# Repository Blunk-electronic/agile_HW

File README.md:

# Demo Project to demonstrate Agile Hardware Development

## Installation
After cloning the repository you have the demo design ready for use.
So far no installation is required.
If you need the module instantiation tool run in the base directory

```
sh install.sh
```

This installs the script [instantiate](instantiate) in your $HOME/bin.

## Module Instantiation

The script script [instantiate](instantiate) renames nets of a module so that
the user is not required to edit them manually via the grapical user interface.
It creates a new schematic and board file with a desired index. 
It requires arguemts in a fixed order. The explanation comes via an example:
```
instantiate led_driver_1.sch LED_DRV 1 3
```
The first argument is the name of the schematic file name. In our case it is led_driver_1.sch.
This file and the associated board file led_driver_1.brd must exist already. It can be regarded
as the generic module.
The second argument LED_DRV is a general prefix that have some net names inside the module.
There is for example a net LED_DRV_1_IN. 
3rd argument is the input index. Prefix and input index compose a string like LED_DRV_1.
The script searches nets that start with the prefix LED_DRV_1 and renames them using
the output index, given by the 4th argument, to LED_DRV_3. Other net names like GND or P3V3
are left as they are.
So the net LED_DRV_1_IN will be renamed to LED_DRV_3_IN.
The script does NOT modify the generic module. It creates a new schematic
and a new board file named led_driver_3.sch and led_driver_3.brd.

The console output is show below:

```
$ instantiate led_driver_1.sch LED_DRV 1 3
input module   : led_driver_1.sch
net prefix     : LED_DRV
index in       : 1
index out      : 3
prefix in full : LED_DRV_1
prefix out full: LED_DRV_3
processing schematic ...
- renaming net LED_DRV_1_IN to LED_DRV_3_IN
- renaming net LED_DRV_1_B to LED_DRV_3_B
- renaming net LED_DRV_1_C to LED_DRV_3_C
- renaming net LED_DRV_1_OUT to LED_DRV_3_OUT
- renaming net LED_DRV_1_IN to LED_DRV_3_IN
processing board ...
- renaming net LED_DRV_1_IN to LED_DRV_3_IN
- renaming net LED_DRV_1_B to LED_DRV_3_B
- renaming net LED_DRV_1_C to LED_DRV_3_C
- renaming net LED_DRV_1_OUT to LED_DRV_3_OUT
generated files:
schematic: led_driver_3.sch
board    : led_driver_3.brd
```

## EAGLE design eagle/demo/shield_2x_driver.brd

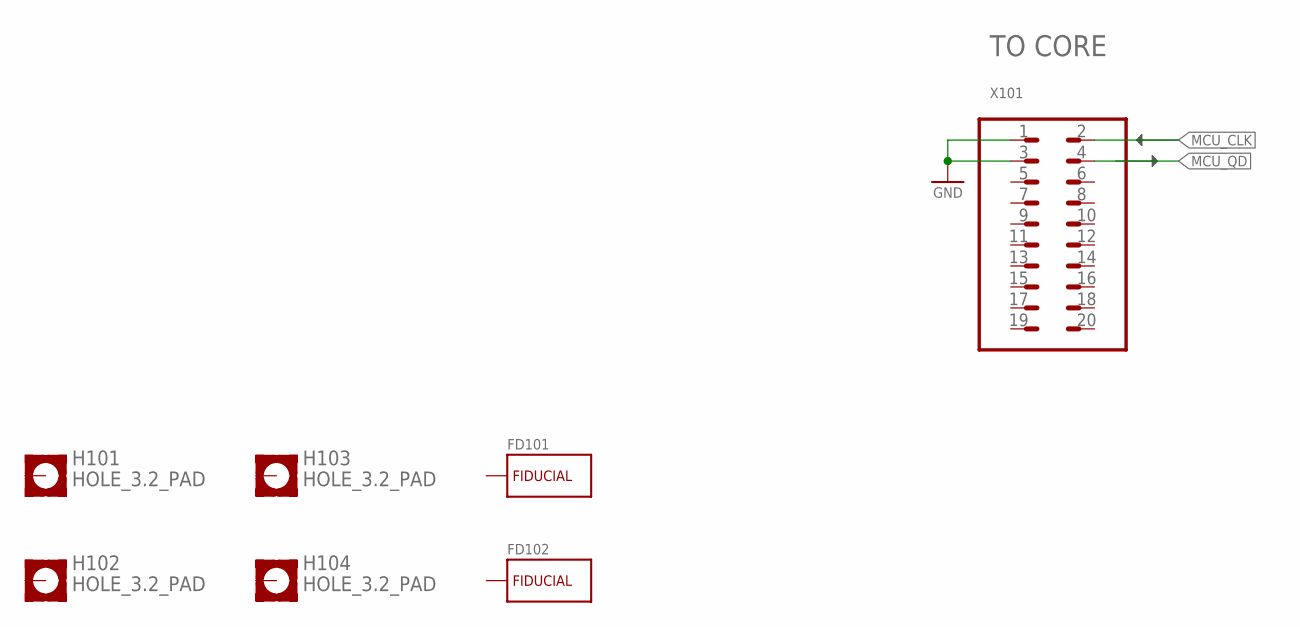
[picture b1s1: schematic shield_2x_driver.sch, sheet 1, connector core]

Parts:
FD101, FD102: FIDUCIAL_CROSSHAIR; CROSSHAIR
H101, H102, H103, H104: HOLE_3.2_PAD; 3.2_PAD
X101: MALE_2X10-T-VERTICAL_2.54MM; T_MALE_2X10_VERTICAL_GRID_2.54MM; PART_CODE_BEL X_PAC_T_MALE_2X10_VERTICAL_PITCH_2mm54

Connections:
GND: X101.1, X101.3; also elsewhere on the board
MCU_CLK: X101.2; also elsewhere on the board
MCU_QD: X101.4; also elsewhere on the board

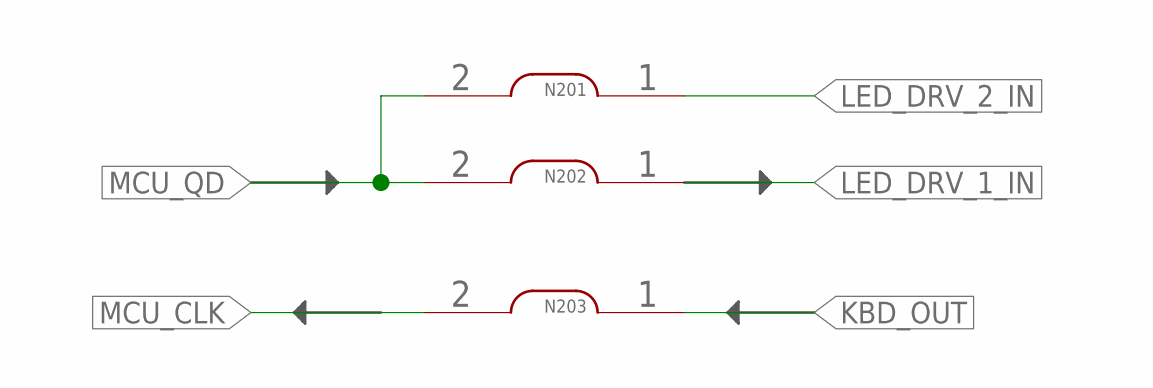
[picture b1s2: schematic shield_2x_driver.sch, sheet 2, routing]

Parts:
N201, N202: NET_CHANGER-S-0.3MM; S_NET_CHANGER_0.3MM
N203: NET_CHANGER-S-0.15MM; S_NET_CHANGER_0.15MM

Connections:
KBD_OUT: N203.1; also elsewhere on the board
LED_DRV_1_IN: N202.1; also elsewhere on the board
LED_DRV_2_IN: N201.1; also elsewhere on the board
MCU_CLK: N203.2; also elsewhere on the board
MCU_QD: N201.2, N202.2; also elsewhere on the board

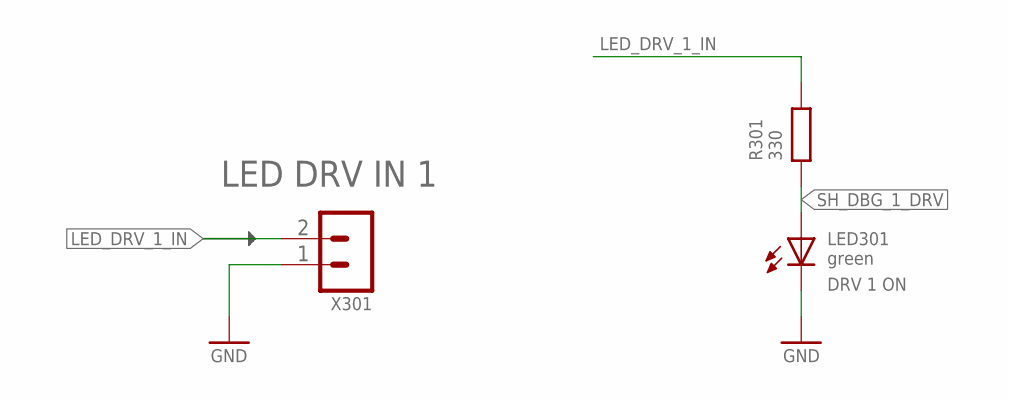
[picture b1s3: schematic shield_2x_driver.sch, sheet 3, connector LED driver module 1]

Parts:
LED301: green; S_0805; PART_CODE_BEL LED_PAC_S_0805_VAL_green
R301: 330; S_0805; PART_CODE_BEL R_PAC_S_0805_VAL_330
X301: MALE_2X1-T-VERTICAL; T_MALE_2X1_VERTICAL_PITCH_2MM54

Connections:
GND: LED301.C, X301.1; also elsewhere on the board
LED_DRV_1_IN: R301.2, X301.2; also elsewhere on the board
SH_DBG_1_DRV: LED301.A, R301.1

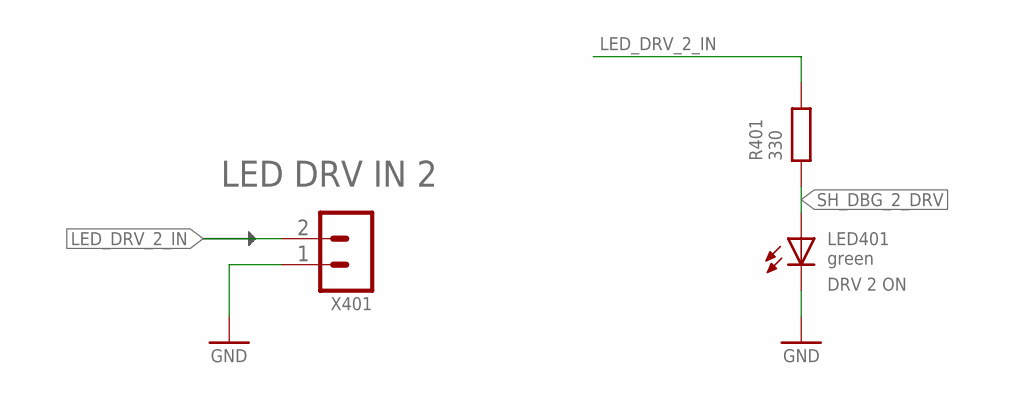
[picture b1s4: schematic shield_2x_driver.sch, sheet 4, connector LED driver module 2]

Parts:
LED401: green; S_0805; PART_CODE_BEL LED_PAC_S_0805_VAL_green
R401: 330; S_0805; PART_CODE_BEL R_PAC_S_0805_VAL_330
X401: MALE_2X1-T-VERTICAL; T_MALE_2X1_VERTICAL_PITCH_2MM54

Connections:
GND: LED401.C, X401.1; also elsewhere on the board
LED_DRV_2_IN: R401.2, X401.2; also elsewhere on the board
SH_DBG_2_DRV: LED401.A, R401.1

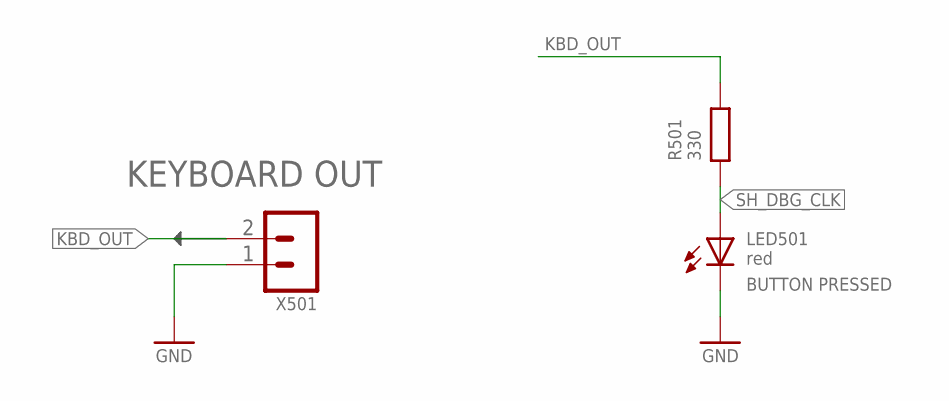
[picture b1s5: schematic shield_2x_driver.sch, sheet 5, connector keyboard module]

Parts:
LED501: red; S_0805; PART_CODE_BEL LED_PAC_S_0805_VAL_red
R501: 330; S_0805; PART_CODE_BEL R_PAC_S_0805_VAL_330
X501: MALE_2X1-T-VERTICAL; T_MALE_2X1_VERTICAL_PITCH_2MM54

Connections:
GND: LED501.C, X501.1; also elsewhere on the board
KBD_OUT: R501.2, X501.2; also elsewhere on the board
SH_DBG_CLK: LED501.A, R501.1

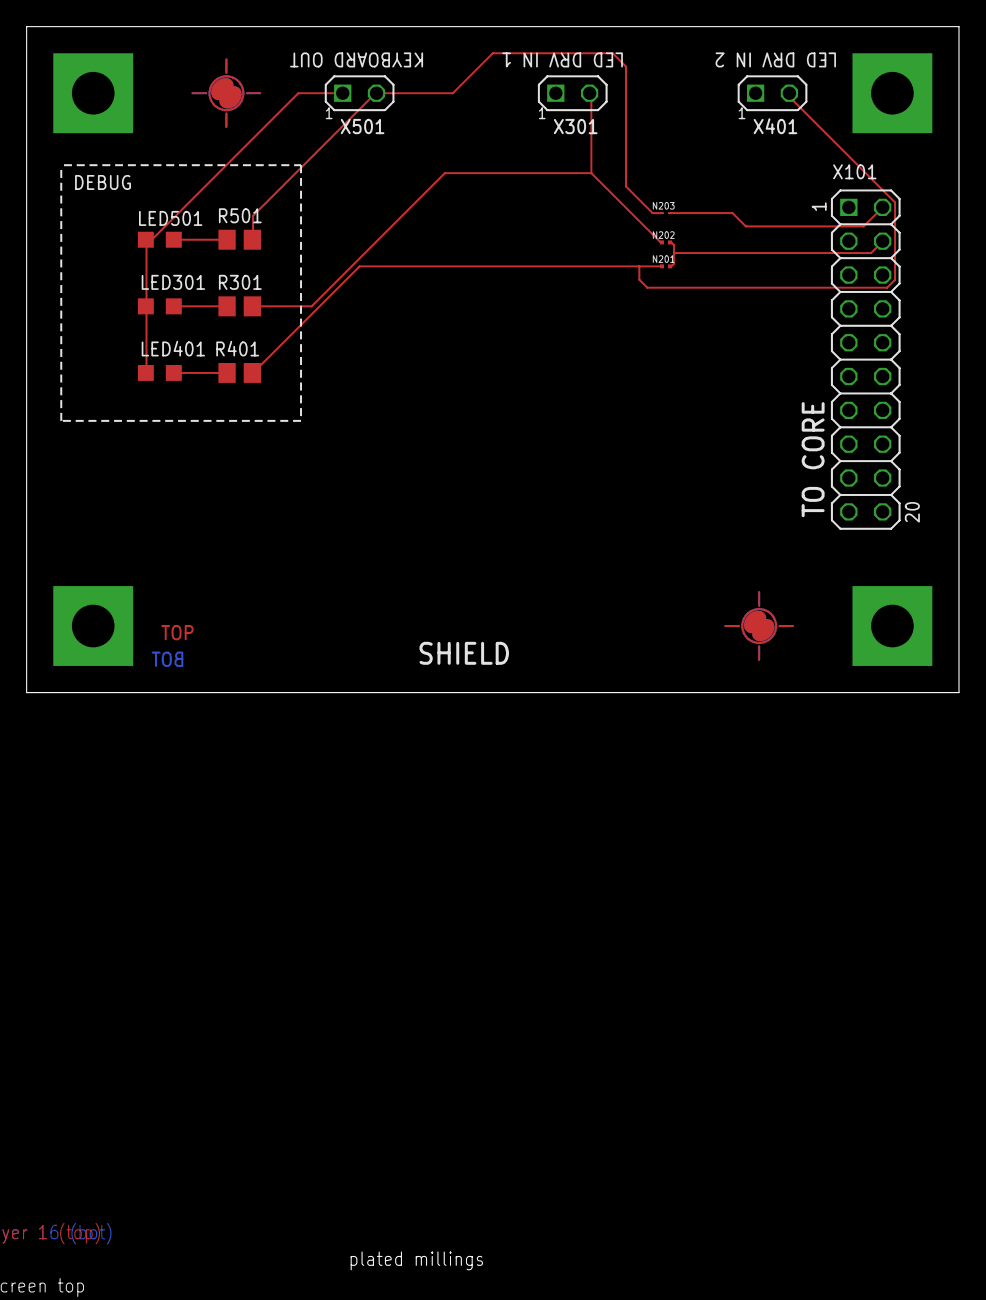
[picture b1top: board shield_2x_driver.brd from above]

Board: 4 copper layers, 70.0 x 93.6 mm, 20 parts (0 on the bottom side), 9 nets.

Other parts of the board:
U$9: A4_LANDSCAPE

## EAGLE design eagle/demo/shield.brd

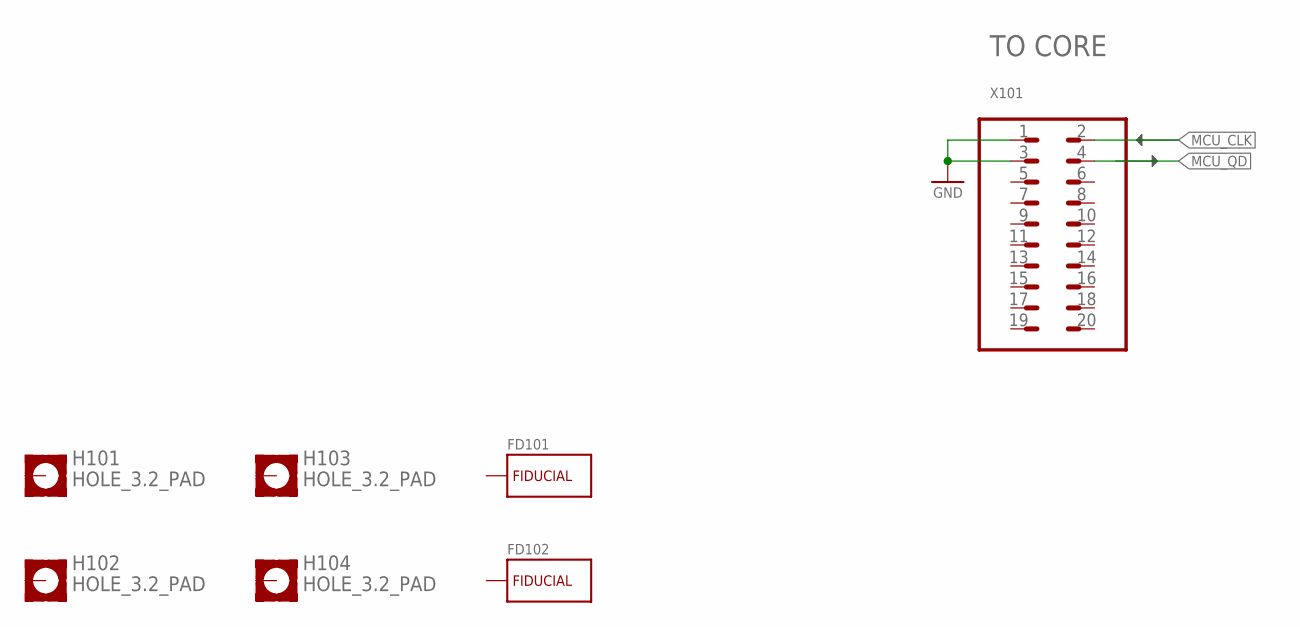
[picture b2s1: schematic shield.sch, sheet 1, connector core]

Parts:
FD101, FD102: FIDUCIAL_CROSSHAIR; CROSSHAIR
H101, H102, H103, H104: HOLE_3.2_PAD; 3.2_PAD
X101: MALE_2X10-T-VERTICAL_2.54MM; T_MALE_2X10_VERTICAL_GRID_2.54MM; PART_CODE_BEL X_PAC_T_MALE_2X10_VERTICAL_PITCH_2mm54

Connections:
GND: X101.1, X101.3; also elsewhere on the board
MCU_CLK: X101.2; also elsewhere on the board
MCU_QD: X101.4; also elsewhere on the board

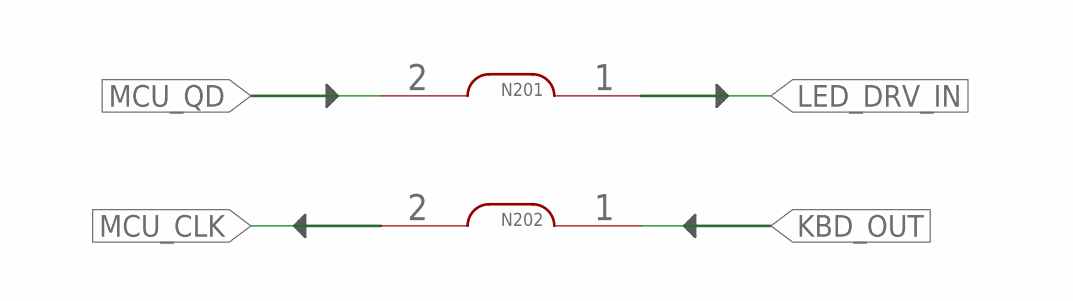
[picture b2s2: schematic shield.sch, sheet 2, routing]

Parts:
N201: NET_CHANGER-S-0.3MM; S_NET_CHANGER_0.3MM
N202: NET_CHANGER-S-0.15MM; S_NET_CHANGER_0.15MM

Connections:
KBD_OUT: N202.1; also elsewhere on the board
LED_DRV_IN: N201.1; also elsewhere on the board
MCU_CLK: N202.2; also elsewhere on the board
MCU_QD: N201.2; also elsewhere on the board

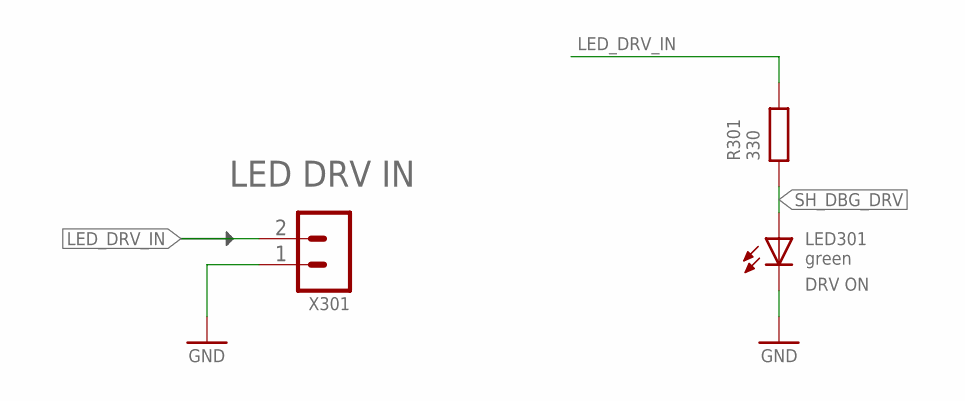
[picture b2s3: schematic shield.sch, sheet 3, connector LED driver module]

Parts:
LED301: green; S_0805; PART_CODE_BEL LED_PAC_S_0805_VAL_green
R301: 330; S_0805; PART_CODE_BEL R_PAC_S_0805_VAL_330
X301: MALE_2X1-T-VERTICAL; T_MALE_2X1_VERTICAL_PITCH_2MM54

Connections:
GND: LED301.C, X301.1; also elsewhere on the board
LED_DRV_IN: R301.2, X301.2; also elsewhere on the board
SH_DBG_DRV: LED301.A, R301.1

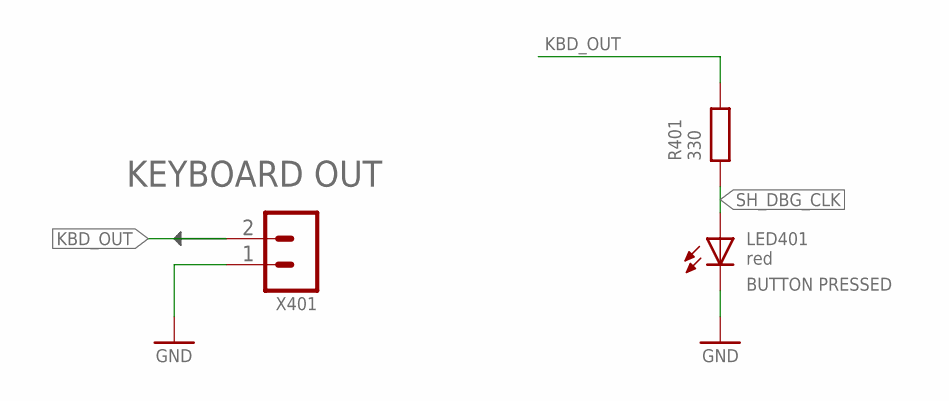
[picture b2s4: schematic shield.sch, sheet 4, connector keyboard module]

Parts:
LED401: red; S_0805; PART_CODE_BEL LED_PAC_S_0805_VAL_red
R401: 330; S_0805; PART_CODE_BEL R_PAC_S_0805_VAL_330
X401: MALE_2X1-T-VERTICAL; T_MALE_2X1_VERTICAL_PITCH_2MM54

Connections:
GND: LED401.C, X401.1; also elsewhere on the board
KBD_OUT: R401.2, X401.2; also elsewhere on the board
SH_DBG_CLK: LED401.A, R401.1

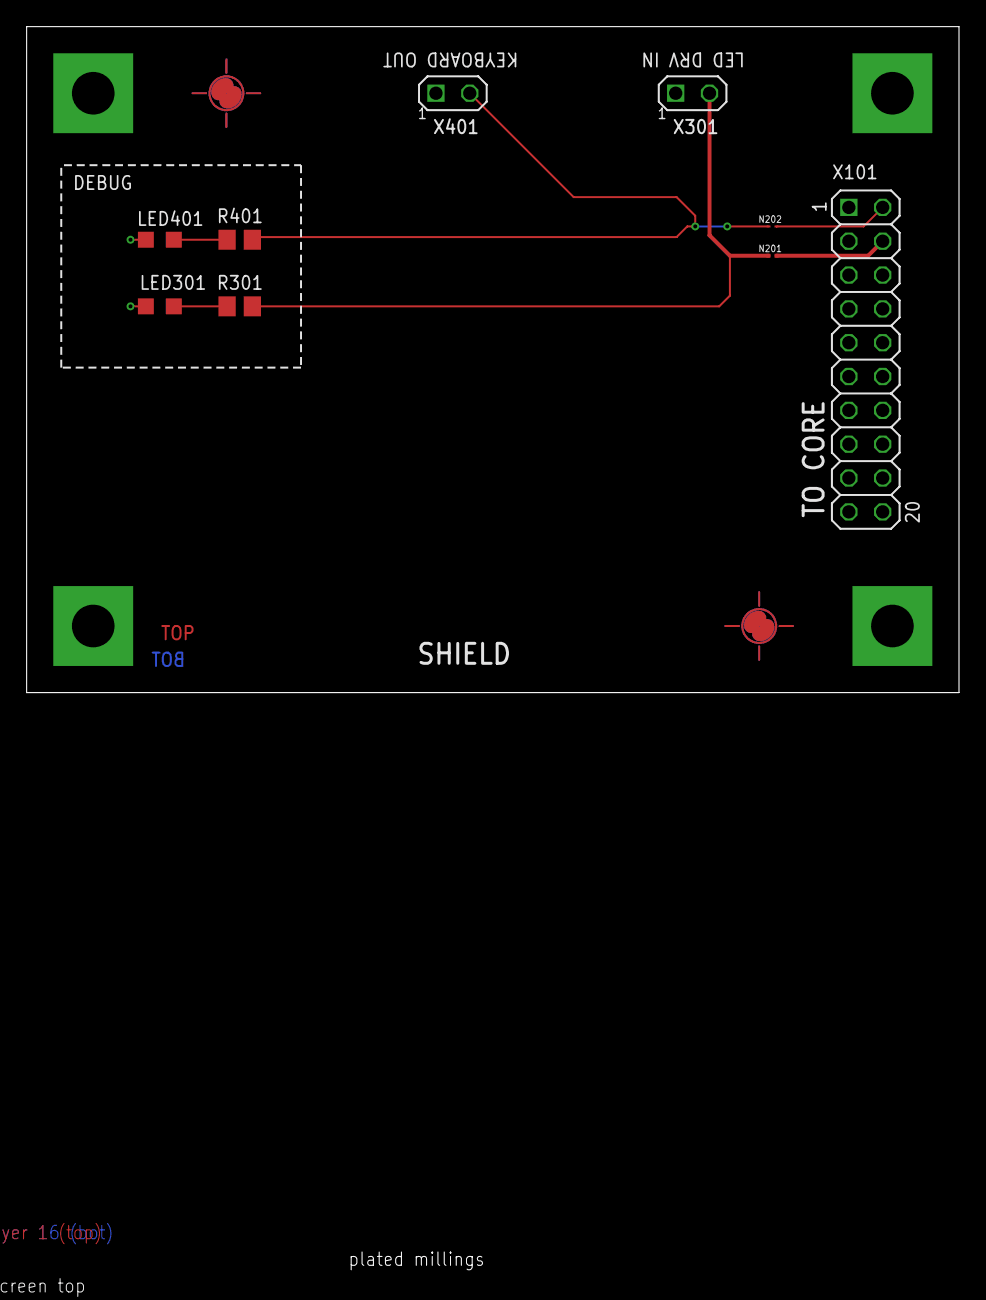
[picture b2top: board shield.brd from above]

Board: 4 copper layers, 70.0 x 93.6 mm, 16 parts (0 on the bottom side), 7 nets.

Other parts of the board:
U$9: A4_LANDSCAPE

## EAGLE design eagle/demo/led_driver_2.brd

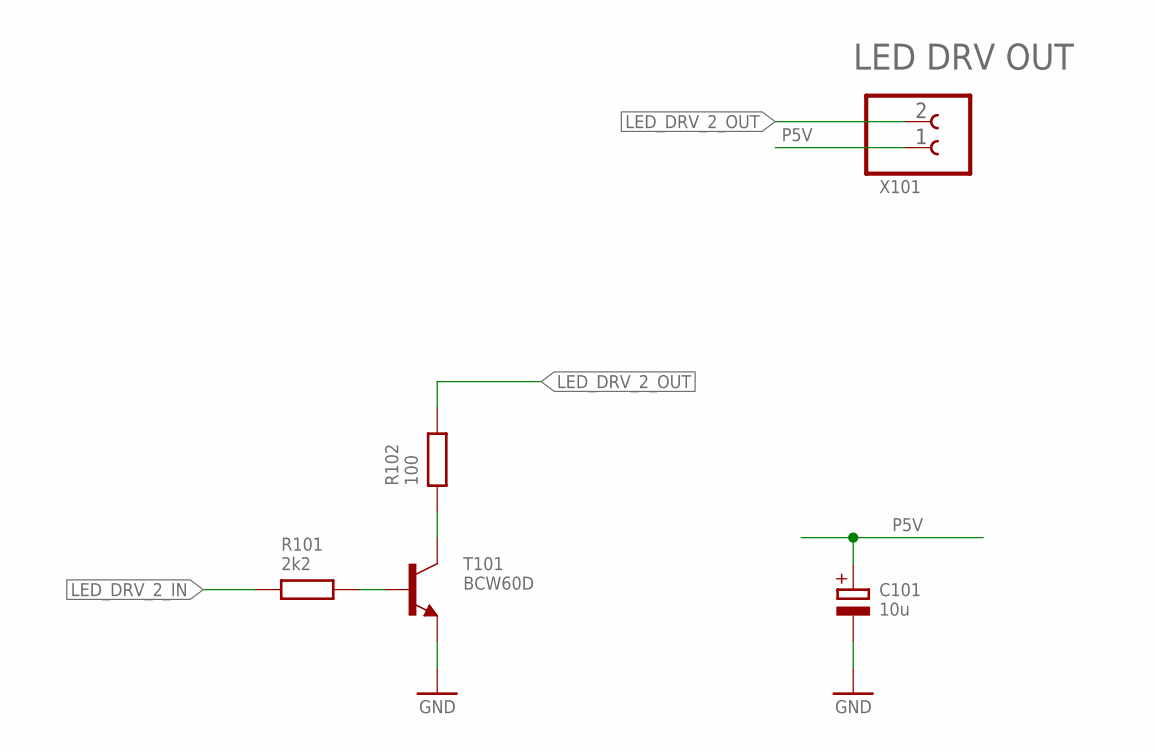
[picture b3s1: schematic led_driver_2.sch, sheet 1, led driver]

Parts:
C101: 10u; S_6032; PART_CODE_BEL C_PAC_S_6032_VAL_10u_Vmax_35V
R101: 2k2; S_0805; PART_CODE_BEL R_PAC_S_0805_VAL_2k2
R102: 100; S_0805; PART_CODE_BEL R_PAC_S_0805_VAL_100
T101: BCW60D; S_SOT23; PART_CODE_BEL T_PAC_S_SOT23_VAL_BCW60D
X101: CLAMP_1X2-T-2.5MM; T_WIRE_CLAMP_1X2_PITCH_2MM5

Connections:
GND: C101.-, T101.2 (E); also elsewhere on the board
LED_DRV_2_B: R101.2, T101.1 (B)
LED_DRV_2_C: R102.1, T101.3 (C)
LED_DRV_2_IN: R101.1; also elsewhere on the board
LED_DRV_2_OUT: R102.2, X101.2
P5V: C101.+, X101.1; also elsewhere on the board

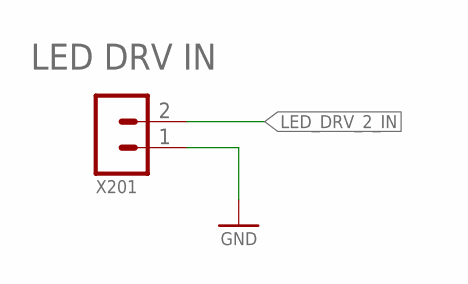
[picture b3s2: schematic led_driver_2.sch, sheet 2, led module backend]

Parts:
X201: MALE_2X1-T-VERTICAL; T_MALE_2X1_VERTICAL_PITCH_2MM54

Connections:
GND: X201.1; also elsewhere on the board
LED_DRV_2_IN: X201.2; also elsewhere on the board

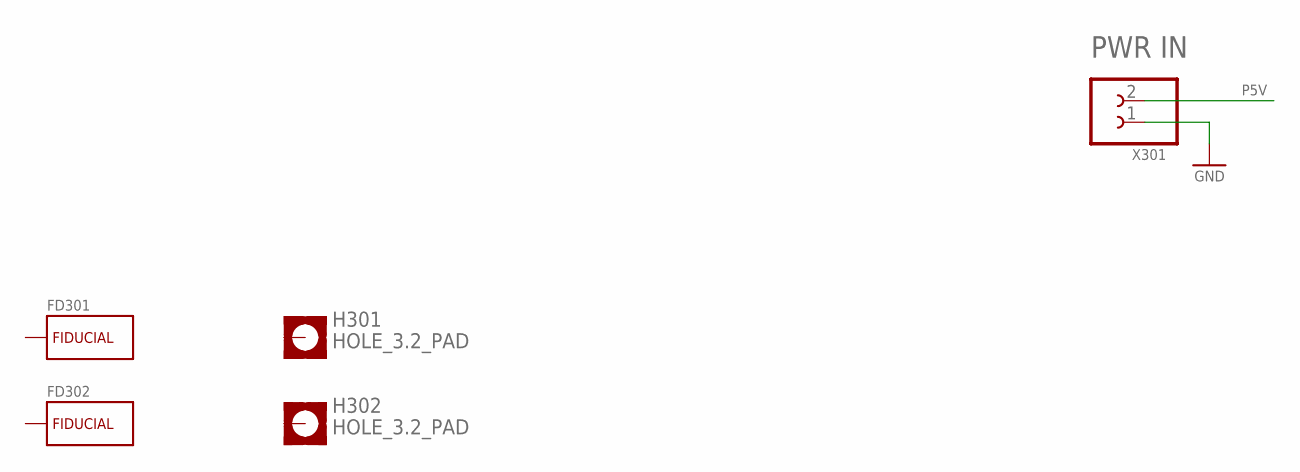
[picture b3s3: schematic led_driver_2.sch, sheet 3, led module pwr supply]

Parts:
FD301, FD302: FIDUCIAL_CROSSHAIR; CROSSHAIR
H301, H302: HOLE_3.2_PAD; 3.2_PAD
X301: CLAMP_1X2-T-2.5MM; T_WIRE_CLAMP_1X2_PITCH_2MM5

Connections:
GND: X301.1; also elsewhere on the board
P5V: X301.2; also elsewhere on the board

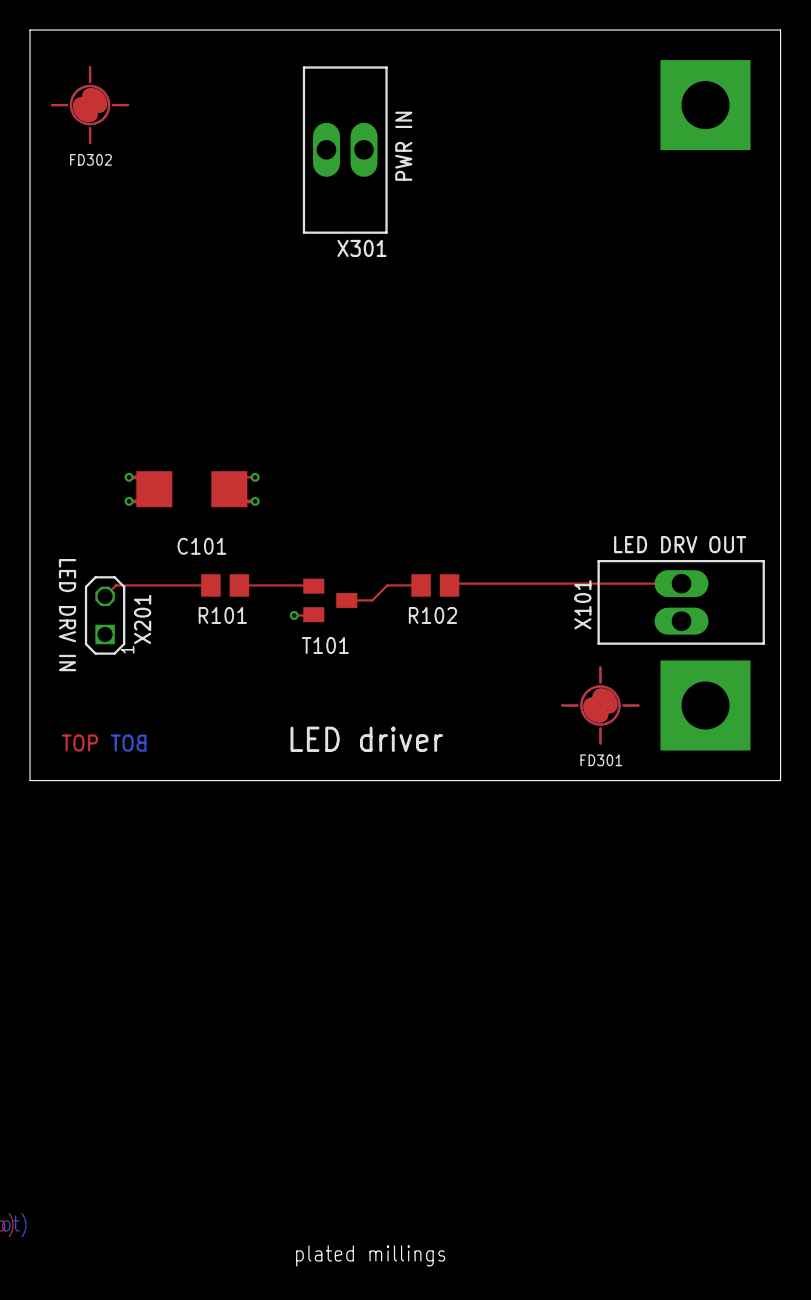
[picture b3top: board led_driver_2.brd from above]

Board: 4 copper layers, 50.0 x 82.6 mm, 12 parts (0 on the bottom side), 6 nets.

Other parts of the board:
U$5: A4_LANDSCAPE

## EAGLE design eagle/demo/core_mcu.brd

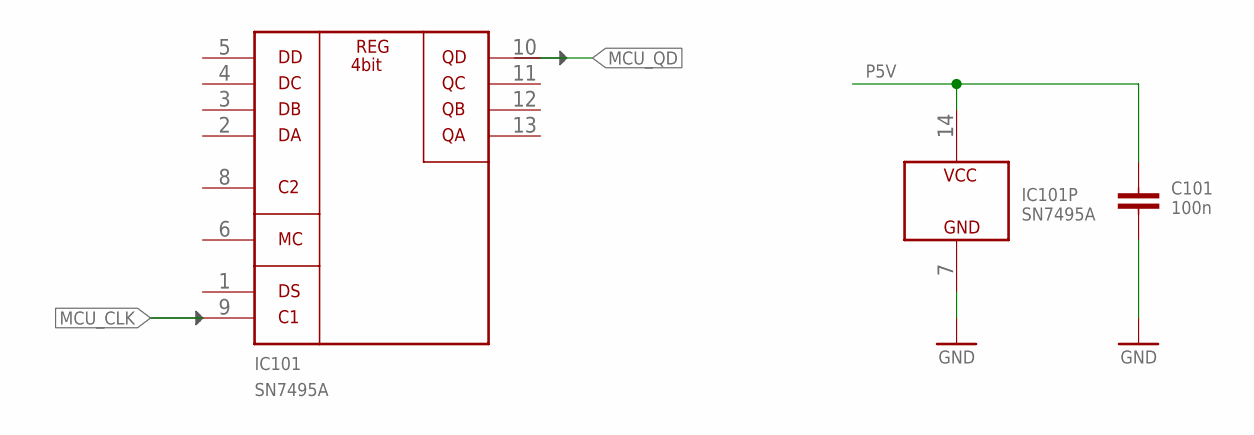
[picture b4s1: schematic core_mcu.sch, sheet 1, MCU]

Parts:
C101: 100n; S_0805; PART_CODE_BEL C_PAC_S_0805_VAL_100n
IC101: SN7495A; T_NDIP14

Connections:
GND: C101.2, IC101.7 (GND); also elsewhere on the board
MCU_CLK: IC101.9 (C1); also elsewhere on the board
MCU_QD: IC101.10 (QD); also elsewhere on the board
P5V: C101.1, IC101.14 (VCC); also elsewhere on the board

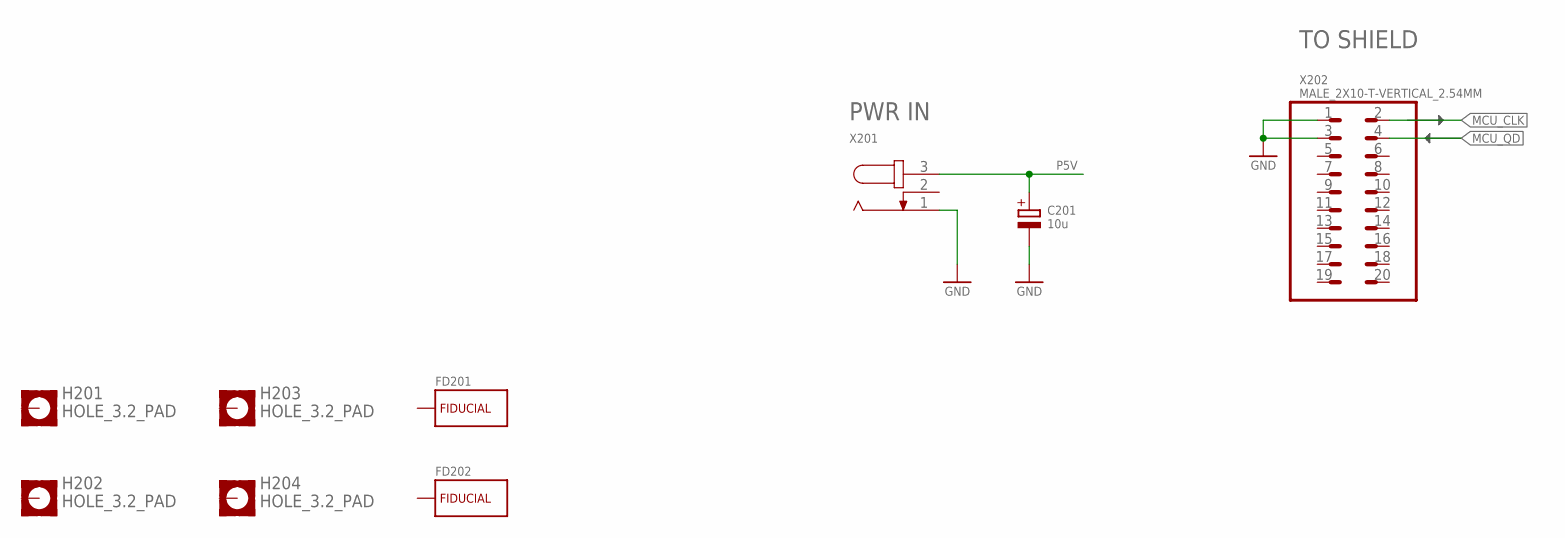
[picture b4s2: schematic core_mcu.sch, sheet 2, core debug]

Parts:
C201: 10u; S_6032; PART_CODE_BEL C_PAC_S_6032_VAL_10u_Vmax_35V
FD201, FD202: FIDUCIAL_CROSSHAIR; CROSSHAIR
H201, H202, H203, H204: HOLE_3.2_PAD; 3.2_PAD
X201: POWER_JACK-T-0; T_POWER_JACK_SPC4077
X202: MALE_2X10-T-VERTICAL_2.54MM; T_MALE_2X10_VERTICAL_GRID_2.54MM; PART_CODE_BEL X_PAC_T_MALE_2X10_VERTICAL_PITCH_2mm54

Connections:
GND: C201.-, X201.1, X202.1, X202.3; also elsewhere on the board
MCU_CLK: X202.2; also elsewhere on the board
MCU_QD: X202.4; also elsewhere on the board
P5V: C201.+, X201.3; also elsewhere on the board

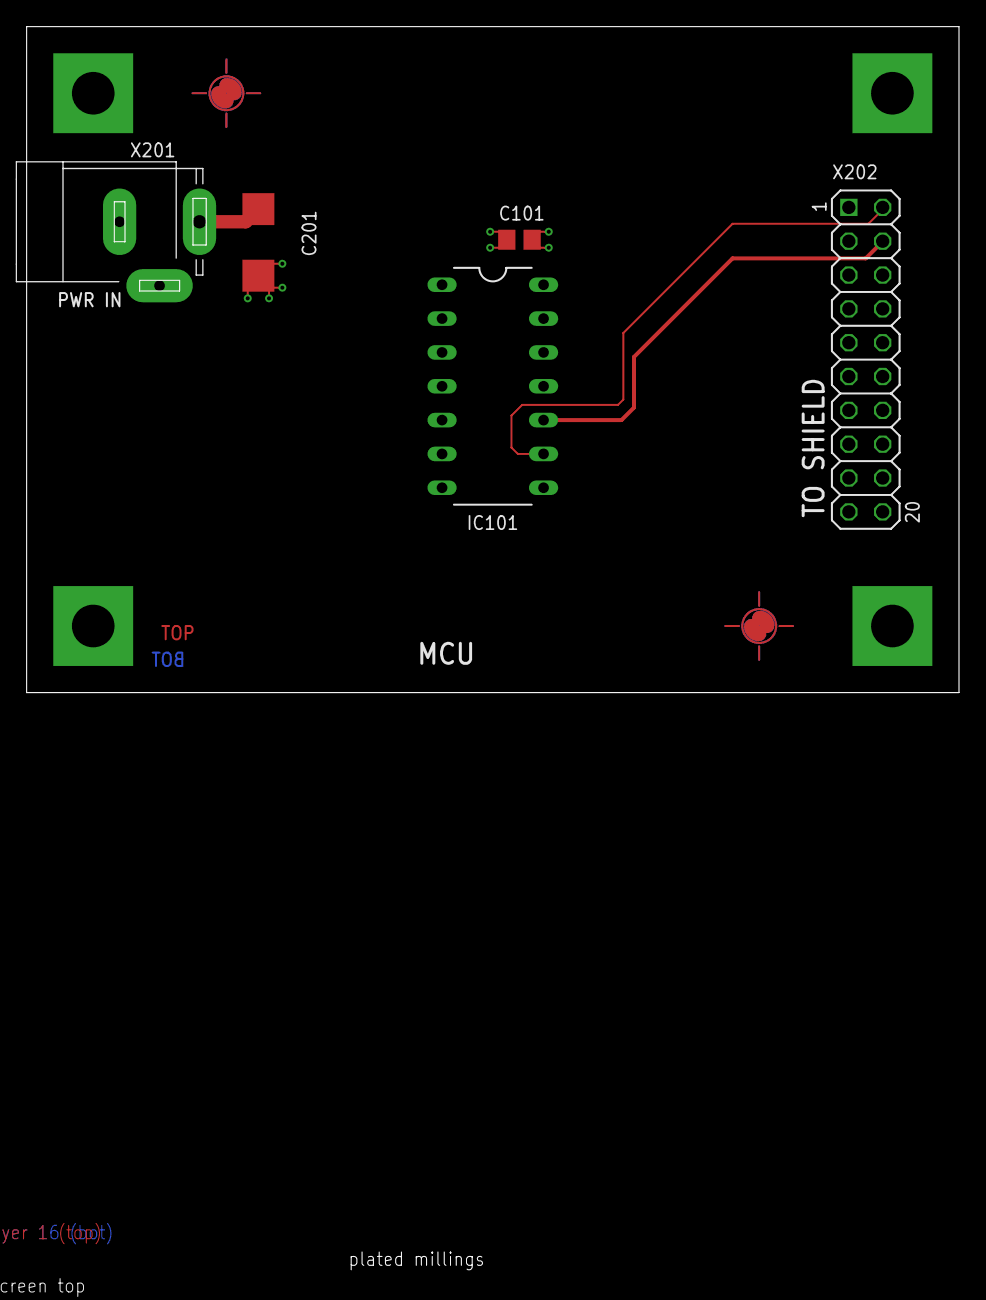
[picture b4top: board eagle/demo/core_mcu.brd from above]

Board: 4 copper layers, 70.0 x 93.6 mm, 12 parts (0 on the bottom side), 4 nets.

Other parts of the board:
U$9: A4_LANDSCAPE

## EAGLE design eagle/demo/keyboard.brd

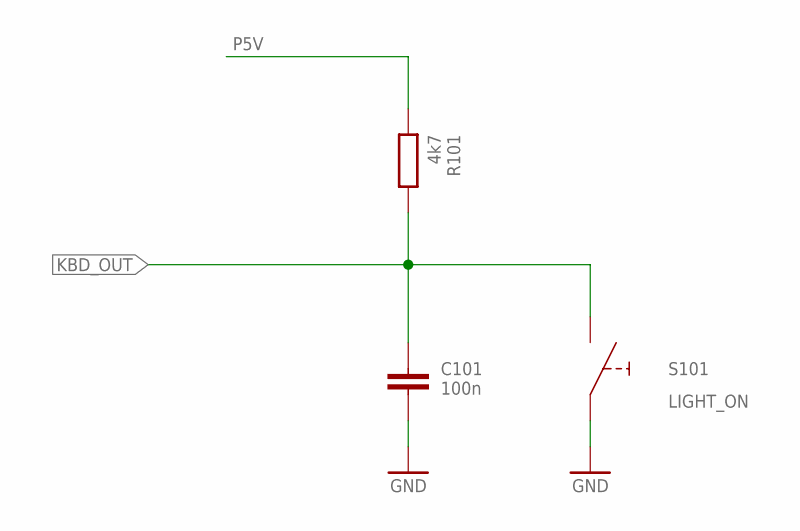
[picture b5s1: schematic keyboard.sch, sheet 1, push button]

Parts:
C101: 100n; S_0805; PART_CODE_BEL C_PAC_S_0805_VAL_100n
R101: 4k7; S_0805; PART_CODE_BEL R_PAC_S_0805_VAL_4k7
S101: PUSH_BUTTON_S_6X6MM; S_PUSH_BUTTON_6X6; PART_CODE_BEL S_PAC_S_PUSH_BUTTON_6X6

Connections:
GND: C101.2, S101.A (A1), S101.A1; also elsewhere on the board
KBD_OUT: C101.1, R101.2, S101.B (B1), S101.B1; also elsewhere on the board
P5V: R101.1; also elsewhere on the board

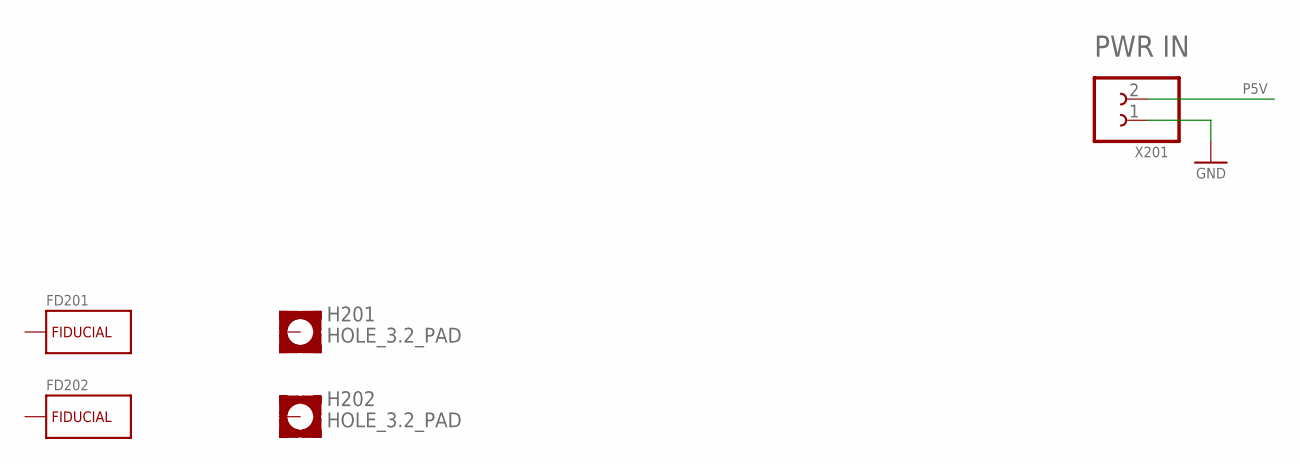
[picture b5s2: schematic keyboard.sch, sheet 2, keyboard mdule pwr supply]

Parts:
FD201, FD202: FIDUCIAL_CROSSHAIR; CROSSHAIR
H201, H202: HOLE_3.2_PAD; 3.2_PAD
X201: CLAMP_1X2-T-2.5MM; T_WIRE_CLAMP_1X2_PITCH_2MM5

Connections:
GND: X201.1; also elsewhere on the board
P5V: X201.2; also elsewhere on the board

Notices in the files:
parts and their libraries:
be_frame: Copyright(C) Blunk electronic
